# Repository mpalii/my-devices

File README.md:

Welcome to the repository with my embedded projects! 🚀

This repository serves as a collection of various embedded systems projects. Whether you're a hobbyist, student, or professional embedded developer, you'll find a diverse range of projects here, spanning across different microcontrollers, development boards, and applications.

Each project within this repository is meticulously crafted to showcase innovative ideas, practical implementations, and efficient utilization of embedded hardware and software. From IoT devices to robotics, sensor applications to automation systems, this repository covers a broad spectrum of embedded technologies.

Feel free to explore, learn, and contribute to the projects. Whether you're looking for inspiration, want to share your own projects, or collaborate with fellow enthusiasts, you've come to the right place. Don't hesitate to fork, clone, or submit pull requests!

Let's build amazing embedded systems together! 💡🛠️

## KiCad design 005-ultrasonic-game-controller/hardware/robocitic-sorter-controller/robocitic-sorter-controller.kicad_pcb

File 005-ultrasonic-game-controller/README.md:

# Gesture-Based Bluetooth Game Controller for Android

Experience touchless control and intuitive gameplay on your Android device!

This wireless game controller is powered by an **ATmega328P** microcontroller and uses an **HC-SR04 ultrasonic sensor** to detect hand gestures as input. Communication is handled via the **HC-05 Bluetooth module**, enabling seamless pairing with Android devices.

Whether you're building a casual game controller, an accessibility tool, or an experimental interface, this project provides a simple and responsive solution for hands-free interaction.

## Features

- 🎮 **Android-compatible** wireless control  
- ✋ **Gesture input** using ultrasonic distance sensing  
- 🔗 **Bluetooth communication** via HC-05 module  
- ⚡ Based on the popular and low-power **ATmega328P MCU**  
- 🧩 Easy to integrate and customize

---

**Coming soon**: Circuit schematics, firmware code, and app integration guide.

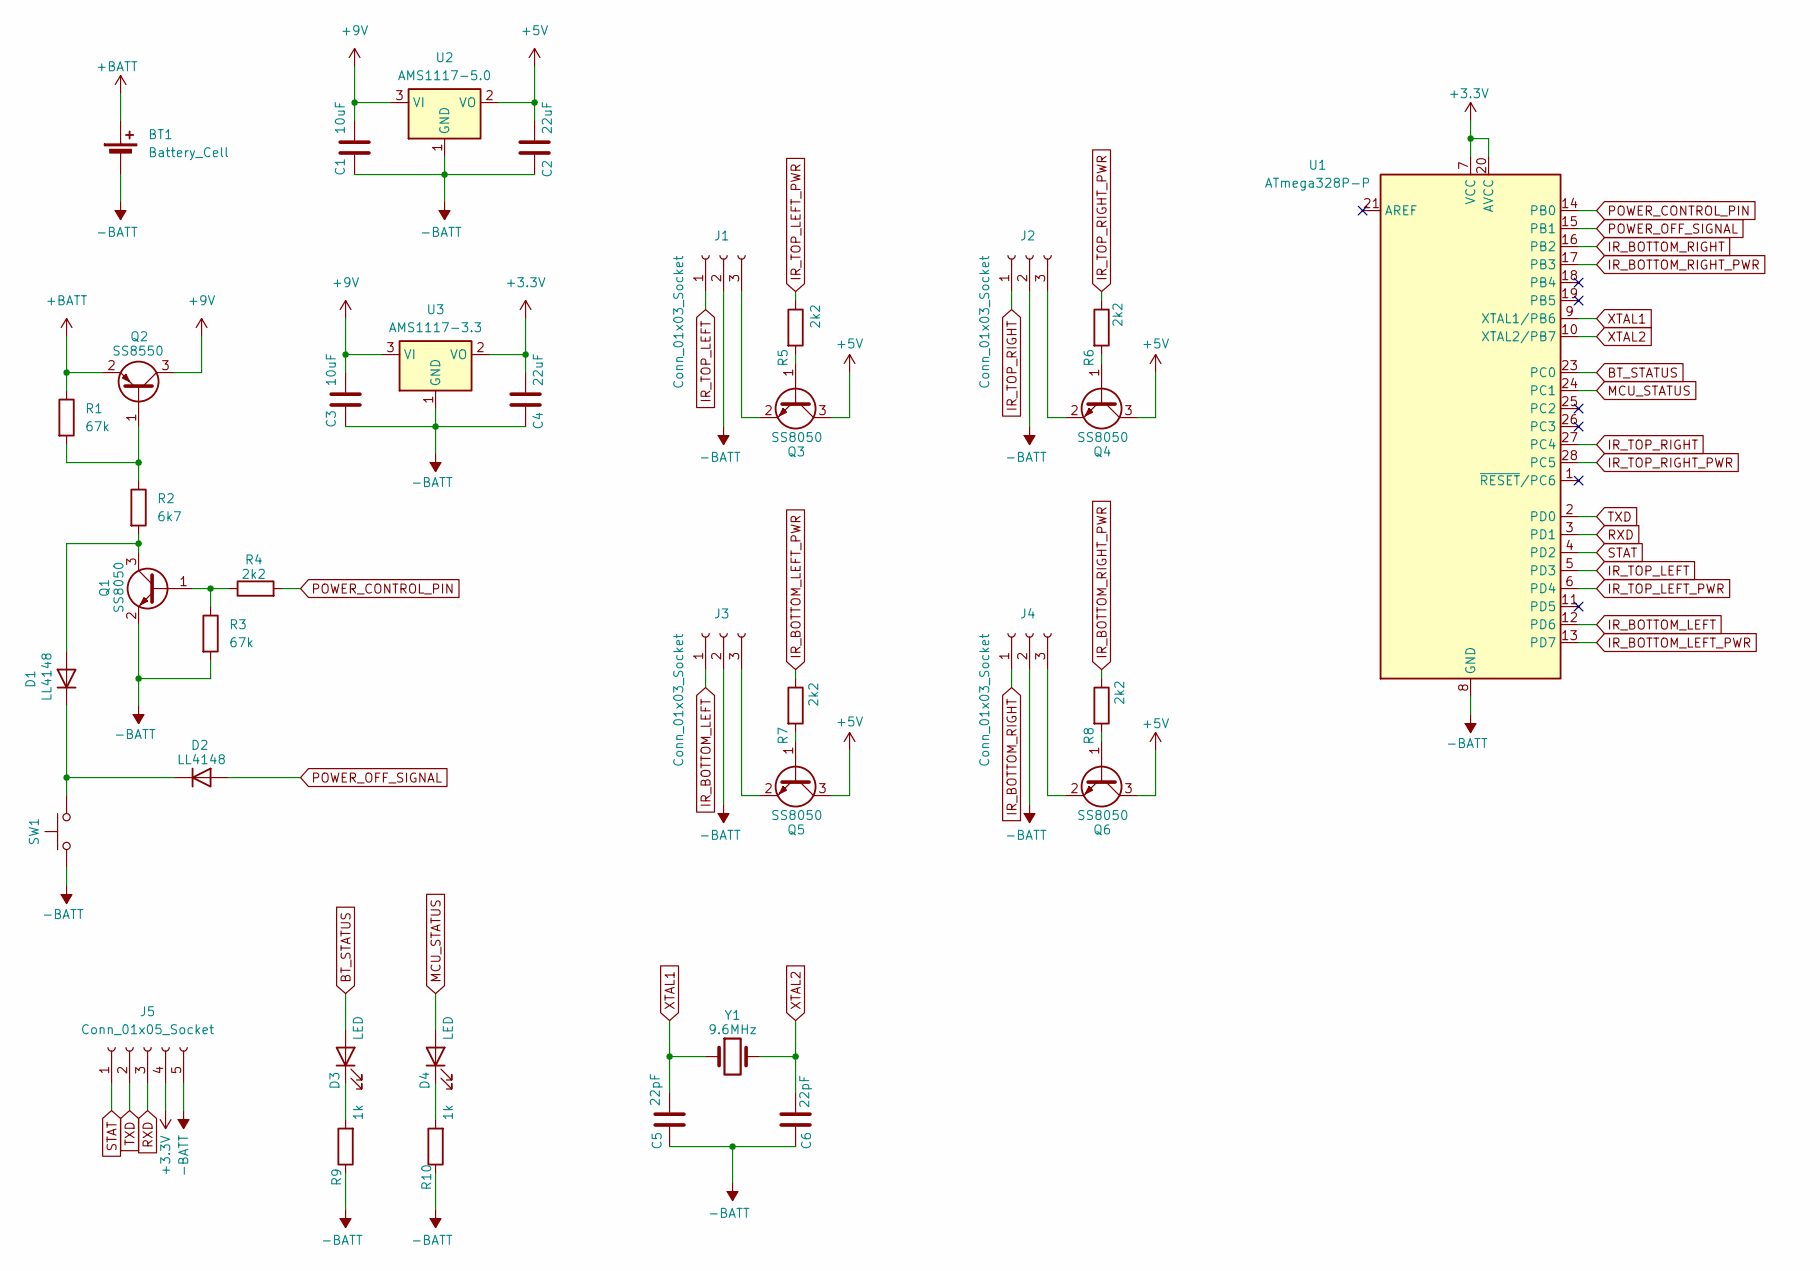
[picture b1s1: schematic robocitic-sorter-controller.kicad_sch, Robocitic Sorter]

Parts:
BT1: Battery_Cell; BatteryHolder_Eagle_12BH611-GR
C1, C3: 10uF; C_0805_2012Metric_Pad1.18x1.45mm_HandSolder
C2, C4: 22uF; C_0805_2012Metric_Pad1.18x1.45mm_HandSolder
C5, C6: 22pF; C_0805_2012Metric_Pad1.18x1.45mm_HandSolder
D1, D2: LL4148; D_MiniMELF_Handsoldering
D3, D4: LED; LED_0805_2012Metric_Pad1.15x1.40mm_HandSolder
J1, J2, J3, J4: Conn_01x03_Socket; PinSocket_1x03_P2.54mm_Vertical
J5: Conn_01x05_Socket; PinSocket_1x05_P2.54mm_Vertical
Q1, Q3, Q4, Q5, Q6: SS8050; SOT-23_Handsoldering
Q2: SS8550; SOT-23_Handsoldering
R1, R3: 67k; R_0805_2012Metric_Pad1.20x1.40mm_HandSolder
R2: 6k7; R_0805_2012Metric_Pad1.20x1.40mm_HandSolder
R4, R5, R6, R7, R8: 2k2; R_0805_2012Metric_Pad1.20x1.40mm_HandSolder
R9, R10: 1k; R_0805_2012Metric_Pad1.20x1.40mm_HandSolder
SW1: SW_Push; SW_PUSH_6mm_H5mm
U1: ATmega328P-P; DIP-28_W7.62mm_Socket_LongPads
U2: AMS1117-5.0; SOT-223-3_TabPin2
U3: AMS1117-3.3; SOT-223-3_TabPin2
Y1: 9.6MHz; Crystal_HC49-4H_Vertical

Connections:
+3.3V: C4.1, J5.4, U1.7 (VCC), U1.20 (AVCC), U3.2 (VO)
+5V: C2.1, Q3.3 (C), Q4.3 (C), Q5.3 (C), Q6.3 (C), U2.2 (VO)
+9V: C1.1, C3.1, Q2.3 (C), U2.3 (VI), U3.3 (VI)
+BATT: BT1.1 (+), Q2.2 (E), R1.1
-BATT: BT1.2 (-), C1.2, C2.2, C3.2, C4.2, C5.2, C6.2, J1.2, J2.2, J3.2, J4.2, J5.5, Q1.2 (E), R3.2, R9.1, R10.1, SW1.1, U1.8 (GND), U1.22 (GND), U2.1 (GND), U3.1 (GND)
BT_STATUS: D3.2 (A), U1.23 (PC0)
IR_BOTTOM_LEFT: J3.1, U1.12 (PD6)
IR_BOTTOM_LEFT_PWR: R7.1, U1.13 (PD7)
IR_BOTTOM_RIGHT: J4.1, U1.16 (PB2)
IR_BOTTOM_RIGHT_PWR: R8.1, U1.17 (PB3)
IR_TOP_LEFT: J1.1, U1.5 (PD3)
IR_TOP_LEFT_PWR: R5.1, U1.6 (PD4)
IR_TOP_RIGHT: J2.1, U1.27 (PC4)
IR_TOP_RIGHT_PWR: R6.1, U1.28 (PC5)
MCU_STATUS: D4.2 (A), U1.24 (PC1)
unnamed: D1.2 (A), Q1.3 (C), R2.2
unnamed: D1.1 (K), D2.1 (K), SW1.2
unnamed: D3.1 (K), R9.2
unnamed: D4.1 (K), R10.2
unnamed: J1.3, Q3.2 (E)
unnamed: J2.3, Q4.2 (E)
unnamed: J3.3, Q5.2 (E)
unnamed: J4.3, Q6.2 (E)
unnamed: Q1.1 (B), R3.1, R4.1
unnamed: Q2.1 (B), R1.2, R2.1
unnamed: Q3.1 (B), R5.2
unnamed: Q4.1 (B), R6.2
unnamed: Q5.1 (B), R7.2
unnamed: Q6.1 (B), R8.2
POWER_CONTROL_PIN: R4.2, U1.14 (PB0)
POWER_OFF_SIGNAL: D2.2 (A), U1.15 (PB1)
RXD: J5.3, U1.3 (PD1)
STAT: J5.1, U1.4 (PD2)
TXD: J5.2, U1.2 (PD0)
XTAL1: C5.1, U1.9 (XTAL1/PB6), Y1.1
XTAL2: C6.1, U1.10 (XTAL2/PB7), Y1.2

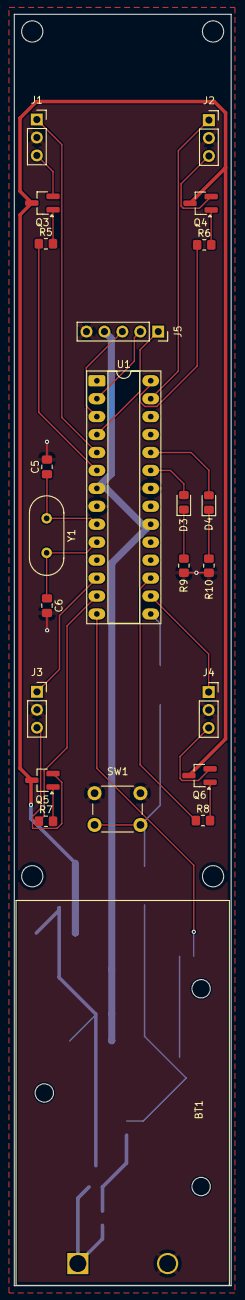
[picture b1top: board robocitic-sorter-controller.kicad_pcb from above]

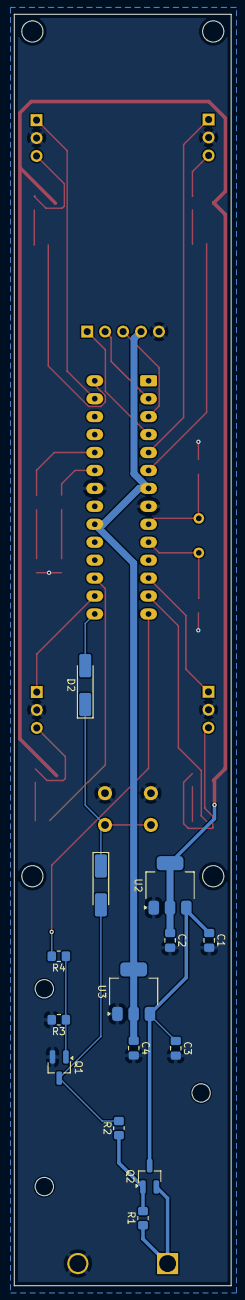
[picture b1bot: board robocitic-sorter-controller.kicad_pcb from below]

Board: 2 copper layers, 30.7 x 180.0 mm, 37 parts (14 on the bottom side), 36 nets.

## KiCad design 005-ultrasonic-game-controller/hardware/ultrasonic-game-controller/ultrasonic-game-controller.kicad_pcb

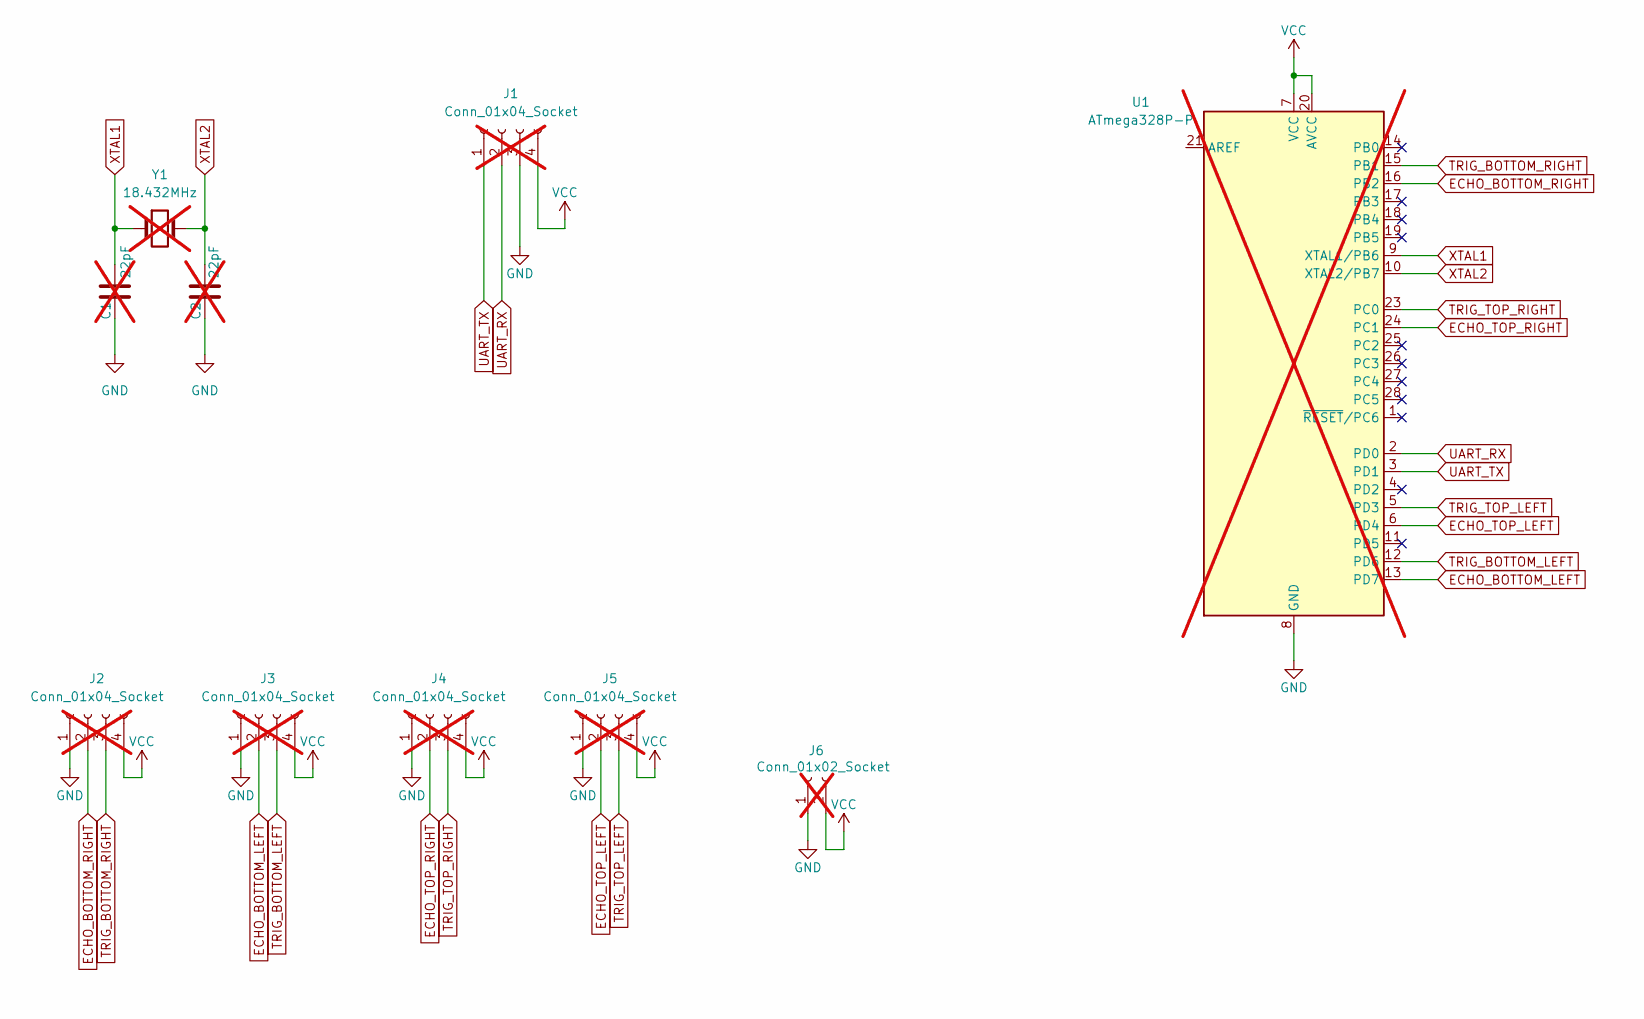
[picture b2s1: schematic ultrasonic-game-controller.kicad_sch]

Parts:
C1, C2: 22pF; C_0805_2012Metric_Pad1.18x1.45mm_HandSolder; not fitted
J1: Conn_01x04_Socket; PinSocket_1x04_P2.54mm_Horizontal; not fitted
J2, J3, J4, J5: Conn_01x04_Socket; PinSocket_1x04_P2.54mm_Vertical; not fitted
J6: Conn_01x02_Socket; PinSocket_1x02_P2.54mm_Vertical; not fitted
U1: ATmega328P-P; DIP-28_W7.62mm_Socket_LongPads; not fitted
Y1: 18.432MHz; Crystal_HC49-4H_Vertical; not fitted

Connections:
ECHO_BOTTOM_LEFT: J3.2, U1.13 (PD7)
ECHO_BOTTOM_RIGHT: J2.2, U1.16 (PB2)
ECHO_TOP_LEFT: J5.2, U1.6 (PD4)
ECHO_TOP_RIGHT: J4.2, U1.24 (PC1)
GND: C1.2, C2.2, J1.3, J2.1, J3.1, J4.1, J5.1, J6.1, U1.8 (GND), U1.22 (GND)
TRIG_BOTTOM_LEFT: J3.3, U1.12 (PD6)
TRIG_BOTTOM_RIGHT: J2.3, U1.15 (PB1)
TRIG_TOP_LEFT: J5.3, U1.5 (PD3)
TRIG_TOP_RIGHT: J4.3, U1.23 (PC0)
UART_RX: J1.2, U1.2 (PD0)
UART_TX: J1.1, U1.3 (PD1)
VCC: J1.4, J2.4, J3.4, J4.4, J5.4, J6.2, U1.7 (VCC), U1.20 (AVCC)
XTAL1: C1.1, U1.9 (XTAL1/PB6), Y1.1
XTAL2: C2.1, U1.10 (XTAL2/PB7), Y1.2

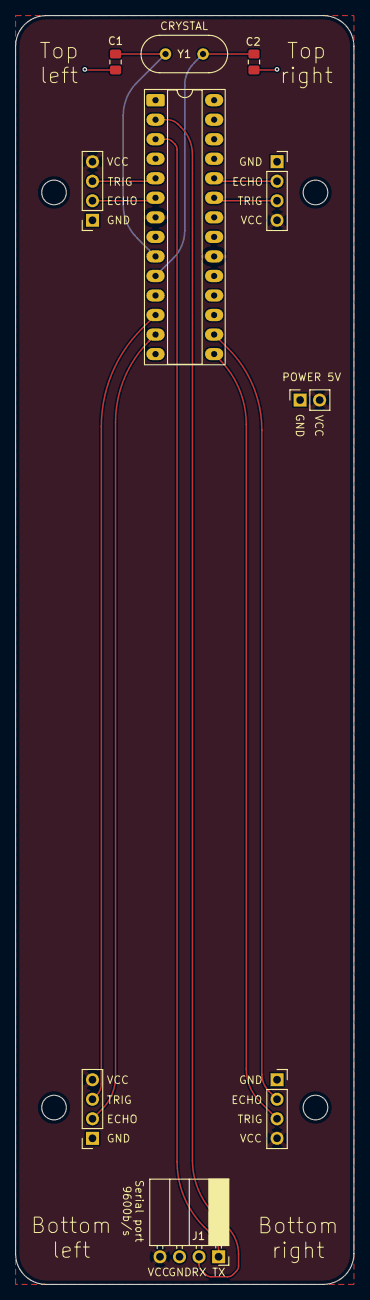
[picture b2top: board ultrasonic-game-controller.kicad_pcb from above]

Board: 2 copper layers, 44.0 x 165.0 mm, 10 parts (0 on the bottom side), 14 nets.

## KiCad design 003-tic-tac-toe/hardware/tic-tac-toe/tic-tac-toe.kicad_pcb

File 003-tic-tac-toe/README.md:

# 003-tic-tac-toe

As a starting point for this project I picked the implementation of [Jim Heaney - Tic Tac Toe](https://github.com/JimHeaney/tic-tac-toe-soldering-kit).  

Difference between Jim's and my versions:
- using SMD components (leds, resistors, capacitors);  
- two selectable playing modes: player versus palyer, player versus algorithm.

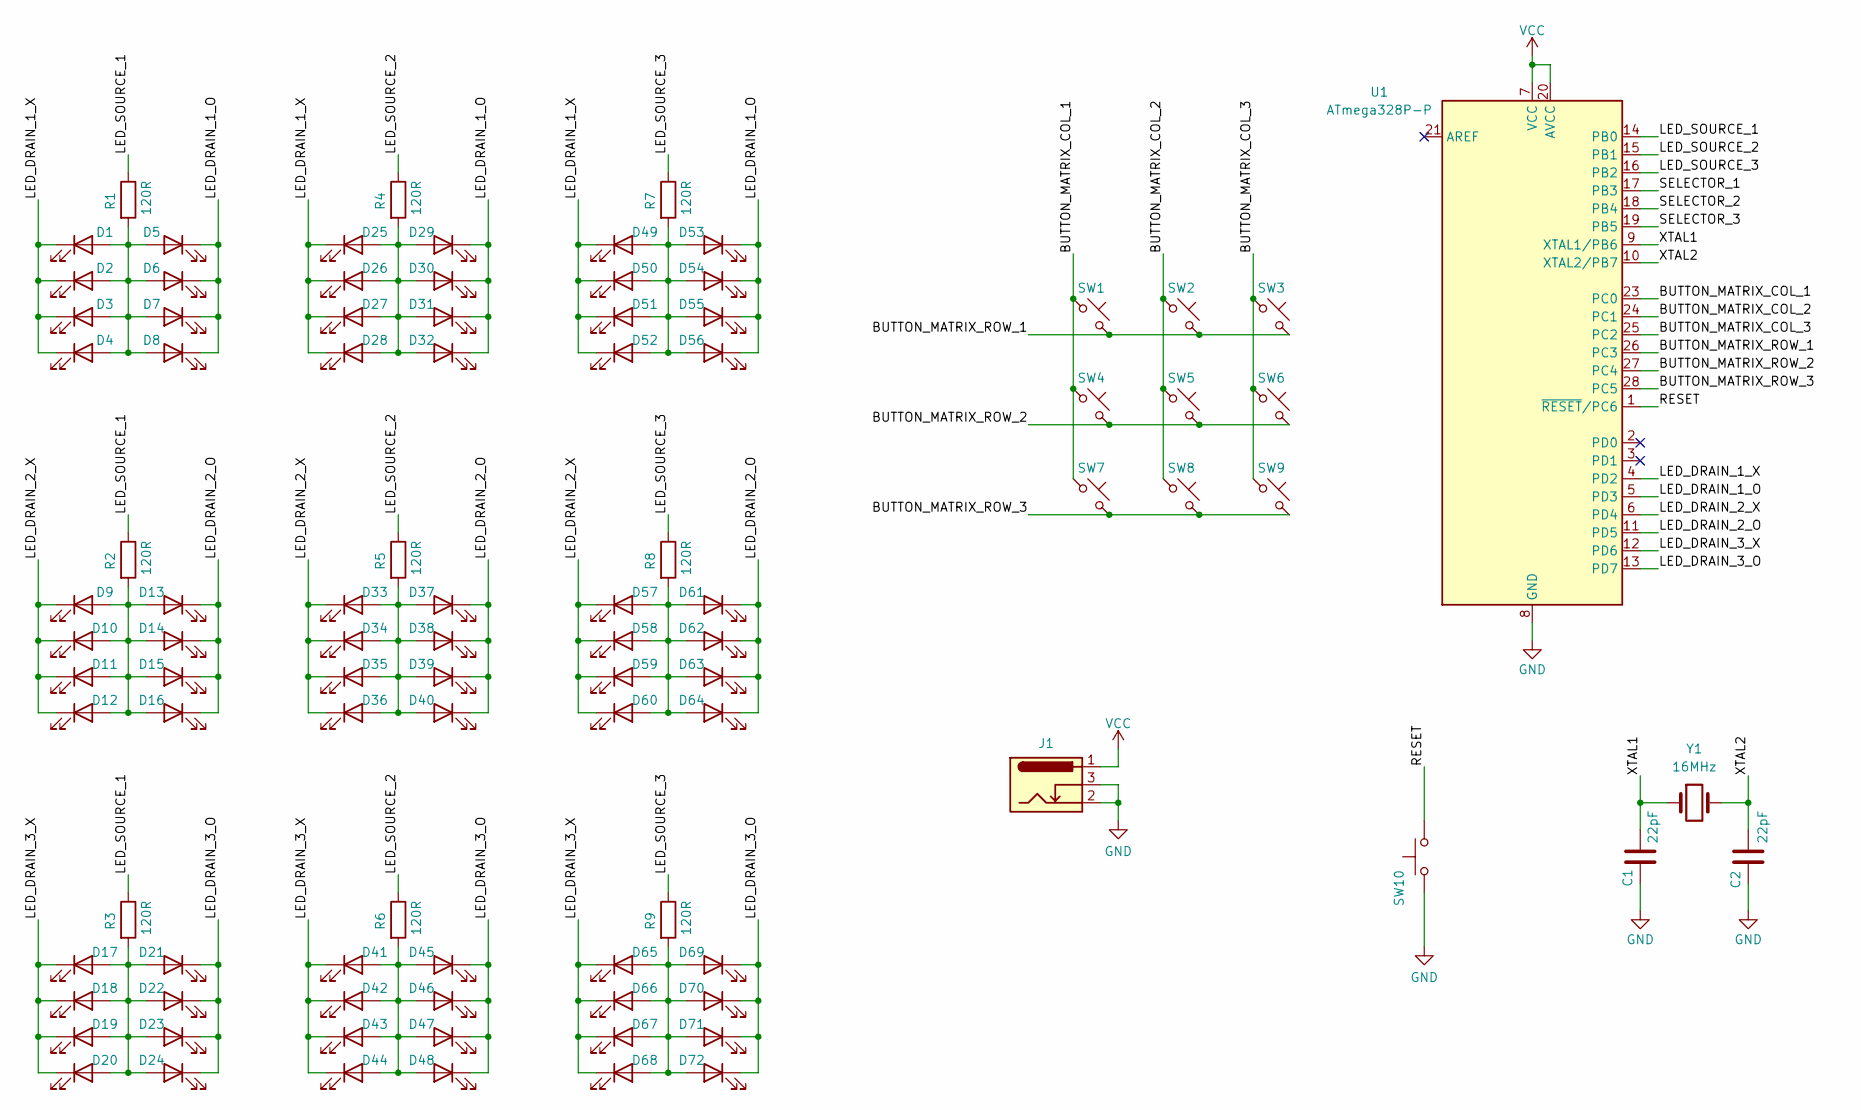
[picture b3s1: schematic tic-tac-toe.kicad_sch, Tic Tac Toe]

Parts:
C1, C2: 22pF; C_0805_2012Metric_Pad1.18x1.45mm_HandSolder
D1, D2, D3, D4, D5, D6, D7, D8, D9, D10, D11, D12, D13, D14, D15, D16, D17, D18, D19, D20, D21, D22, D23, D24, D25, D26, D27, D28, D29, D30, D31, D32, D33, D34, D35, D36, D37, D38, D39, D40, D41, D42, D43, D44, D45, D46, D47, D48, D49, D50, D51, D52, D53, D54, D55, D56, D57, D58, D59, D60, D61, D62, D63, D64, D65, D66, D67, D68, D69, D70, D71, D72: LED; LED_0805_2012Metric_Pad1.15x1.40mm_HandSolder
J1: Barrel_Jack_Switch; BarrelJack_GCT_DCJ200-10-A_Horizontal
R1, R2, R3, R4, R5, R6, R7, R8, R9: 120R; R_0805_2012Metric_Pad1.20x1.40mm_HandSolder
SW1, SW2, SW3, SW4, SW5, SW6, SW7, SW8, SW9: SW_Push_45deg; SW_PUSH_6mm_H5mm
SW10: SW_Push; SW_PUSH_6mm_H5mm
U1: ATmega328P-P; DIP-28_W7.62mm_Socket
Y1: 16MHz; Crystal_HC49-4H_Vertical

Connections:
/BUTTON_MATRIX_COL_1: SW1.1, SW4.1, SW7.1, U1.23 (PC0)
/BUTTON_MATRIX_COL_2: SW2.1, SW5.1, SW8.1, U1.24 (PC1)
/BUTTON_MATRIX_COL_3: SW3.1, SW6.1, SW9.1, U1.25 (PC2)
/BUTTON_MATRIX_ROW_1: SW1.2, SW2.2, SW3.2, U1.26 (PC3)
/BUTTON_MATRIX_ROW_2: SW4.2, SW5.2, SW6.2, U1.27 (PC4)
/BUTTON_MATRIX_ROW_3: SW7.2, SW8.2, SW9.2, U1.28 (PC5)
/LED_DRAIN_1_O: D5.1 (K), D6.1 (K), D7.1 (K), D8.1 (K), D29.1 (K), D30.1 (K), D31.1 (K), D32.1 (K), D53.1 (K), D54.1 (K), D55.1 (K), D56.1 (K), U1.5 (PD3)
/LED_DRAIN_1_X: D1.1 (K), D2.1 (K), D3.1 (K), D4.1 (K), D25.1 (K), D26.1 (K), D27.1 (K), D28.1 (K), D49.1 (K), D50.1 (K), D51.1 (K), D52.1 (K), U1.4 (PD2)
/LED_DRAIN_2_O: D13.1 (K), D14.1 (K), D15.1 (K), D16.1 (K), D37.1 (K), D38.1 (K), D39.1 (K), D40.1 (K), D61.1 (K), D62.1 (K), D63.1 (K), D64.1 (K), U1.11 (PD5)
/LED_DRAIN_2_X: D9.1 (K), D10.1 (K), D11.1 (K), D12.1 (K), D33.1 (K), D34.1 (K), D35.1 (K), D36.1 (K), D57.1 (K), D58.1 (K), D59.1 (K), D60.1 (K), U1.6 (PD4)
/LED_DRAIN_3_O: D21.1 (K), D22.1 (K), D23.1 (K), D24.1 (K), D45.1 (K), D46.1 (K), D47.1 (K), D48.1 (K), D69.1 (K), D70.1 (K), D71.1 (K), D72.1 (K), U1.13 (PD7)
/LED_DRAIN_3_X: D17.1 (K), D18.1 (K), D19.1 (K), D20.1 (K), D41.1 (K), D42.1 (K), D43.1 (K), D44.1 (K), D65.1 (K), D66.1 (K), D67.1 (K), D68.1 (K), U1.12 (PD6)
/LED_SOURCE_1: R1.1, R2.1, R3.1, U1.14 (PB0)
/LED_SOURCE_2: R4.1, R5.1, R6.1, U1.15 (PB1)
/LED_SOURCE_3: R7.1, R8.1, R9.1, U1.16 (PB2)
/RESET: SW10.2, U1.1 (~RESET/PC6)
/SELECTOR_1: U1.17 (PB3)
/SELECTOR_2: U1.18 (PB4)
/SELECTOR_3: U1.19 (PB5)
/XTAL1: C1.1, U1.9 (XTAL1/PB6), Y1.1
/XTAL2: C2.1, U1.10 (XTAL2/PB7), Y1.2
GND: C1.2, C2.2, J1.2, J1.3, SW10.1, U1.8 (GND), U1.22 (GND)
unnamed: D1.2 (A), D2.2 (A), D3.2 (A), D4.2 (A), D5.2 (A), D6.2 (A), D7.2 (A), D8.2 (A), R1.2
unnamed: D9.2 (A), D10.2 (A), D11.2 (A), D12.2 (A), D13.2 (A), D14.2 (A), D15.2 (A), D16.2 (A), R2.2
unnamed: D17.2 (A), D18.2 (A), D19.2 (A), D20.2 (A), D21.2 (A), D22.2 (A), D23.2 (A), D24.2 (A), R3.2
unnamed: D25.2 (A), D26.2 (A), D27.2 (A), D28.2 (A), D29.2 (A), D30.2 (A), D31.2 (A), D32.2 (A), R4.2
unnamed: D33.2 (A), D34.2 (A), D35.2 (A), D36.2 (A), D37.2 (A), D38.2 (A), D39.2 (A), D40.2 (A), R5.2
unnamed: D41.2 (A), D42.2 (A), D43.2 (A), D44.2 (A), D45.2 (A), D46.2 (A), D47.2 (A), D48.2 (A), R6.2
unnamed: D49.2 (A), D50.2 (A), D51.2 (A), D52.2 (A), D53.2 (A), D54.2 (A), D55.2 (A), D56.2 (A), R7.2
unnamed: D57.2 (A), D58.2 (A), D59.2 (A), D60.2 (A), D61.2 (A), D62.2 (A), D63.2 (A), D64.2 (A), R8.2
unnamed: D65.2 (A), D66.2 (A), D67.2 (A), D68.2 (A), D69.2 (A), D70.2 (A), D71.2 (A), D72.2 (A), R9.2
VCC: J1.1, U1.7 (VCC), U1.20 (AVCC)

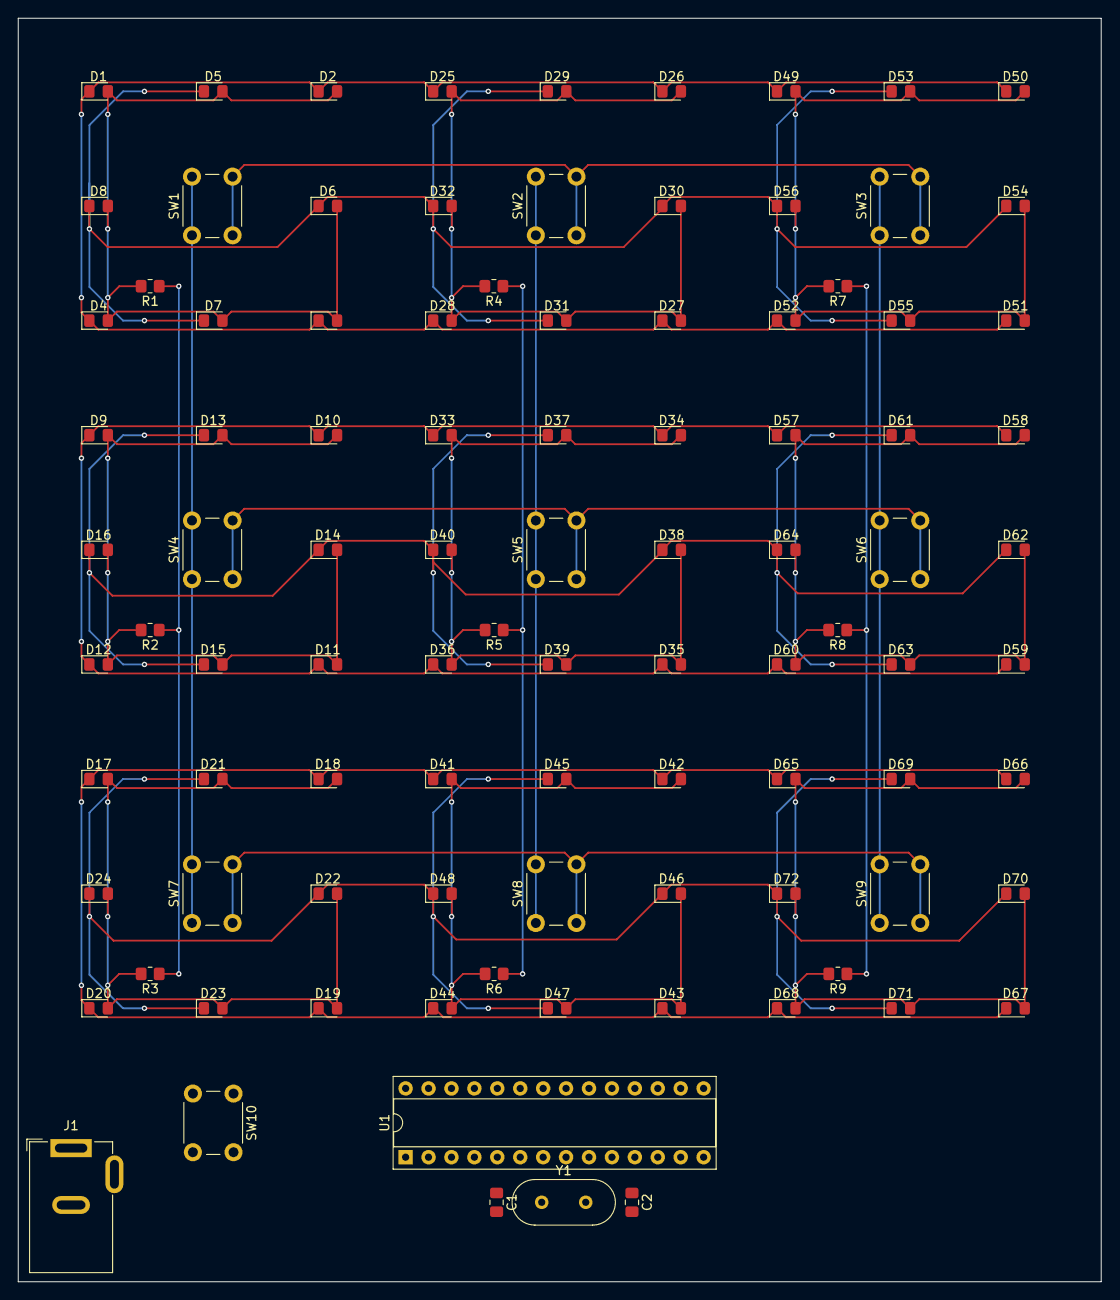
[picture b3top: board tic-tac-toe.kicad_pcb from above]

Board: 2 copper layers, 120.0 x 140.0 mm, 96 parts (0 on the bottom side), 29 nets.

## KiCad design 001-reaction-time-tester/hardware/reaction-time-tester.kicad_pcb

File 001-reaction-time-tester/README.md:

# Reaction Time Measurement System  

## Overview
This project implements a reaction time measurement system using an AVR microcontroller (mega328p). The system measures the time taken for a user to react to a stimulus and displays the results on an LCD screen.  
In fact this is an assigment for laboratory work #1 from Cornell University ECE 4760 course - Spring 2012.  

## Features
- **High Precision:** Measures reaction time with 16µs resolution.
- **User-Friendly Display:** Outputs results on an LCD screen.
- **Score Persistence:** Saves high scores in EEPROM memory.
- **PC Connectivity:** UART communication for monitoring and debugging.

## How to Use
1. **Hardware Setup:**
   - Connect the AVR microcontroller to the required peripherals (buttons, LCD, buzzer, etc.).
   - Assemble the PCB as outlined in the KiCad design files.

2. **Firmware Deployment:**
   - Use the provided `Makefile` to build the project using the AVR GCC toolchain.
   - Upload the firmware to the microcontroller using AVRDUDE.

3. **Operation:**
   - Power the device and follow the on-screen prompts.
   - Monitor reaction times on the LCD and see the system information using the UART interface.

4. **Simulation:**
   - Run the simulation using Proteus for testing and debugging without hardware.

## Dependencies
- AVR GCC Toolchain
- AVRDUDE for uploading firmware
- Terminal program for UART communication

## License
This project is licensed under the [MIT License](LICENSE).

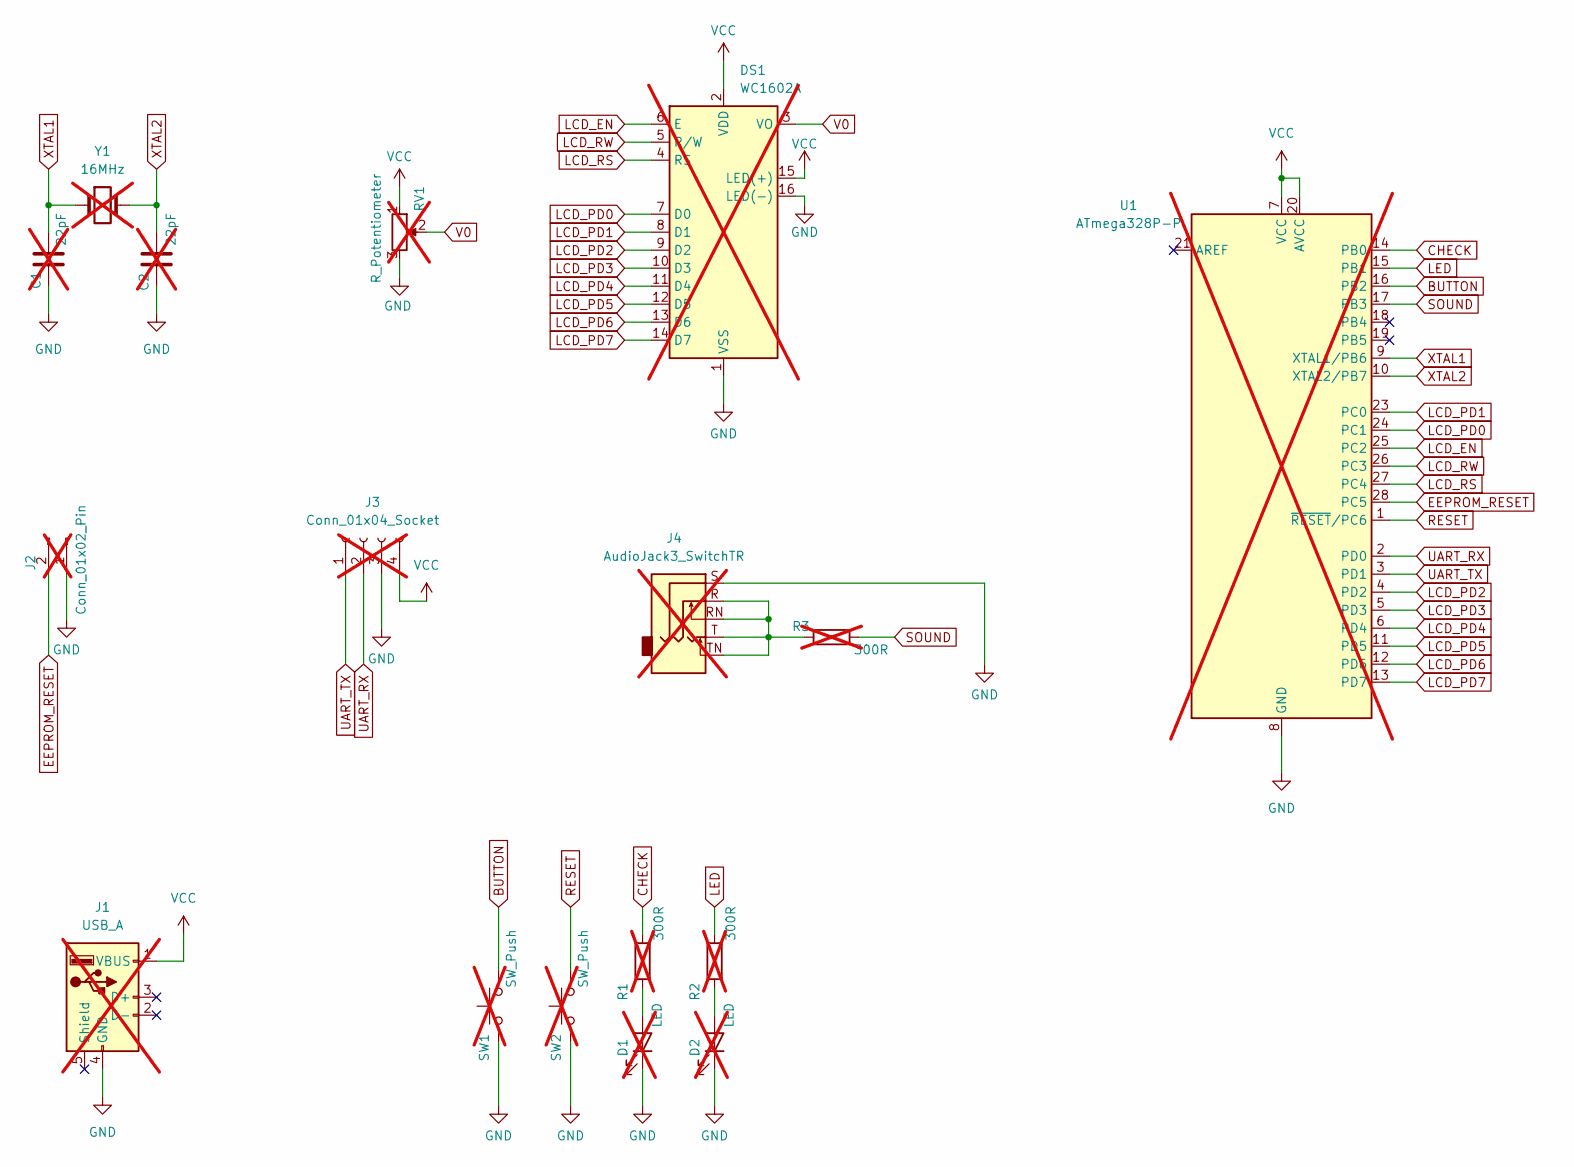
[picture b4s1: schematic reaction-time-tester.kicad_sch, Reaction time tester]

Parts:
C1, C2: 22pF; C_0805_2012Metric_Pad1.18x1.45mm_HandSolder; not fitted
D1, D2: LED; LED_0805_2012Metric_Pad1.15x1.40mm_HandSolder; not fitted
DS1: WC1602A; not fitted
J1: USB_A; USB_A_CONNFLY_DS1095-WNR0; not fitted
J2: Conn_01x02_Pin; PinHeader_1x02_P2.54mm_Vertical; not fitted
J3: Conn_01x04_Socket; PinSocket_1x04_P2.54mm_Horizontal; not fitted
J4: AudioJack3_SwitchTR; Jack_3.5mm_CUI_SJ1-3525N_Horizontal; not fitted
R1, R2, R3: 300R; R_0805_2012Metric_Pad1.20x1.40mm_HandSolder; not fitted
RV1: R_Potentiometer; Potentiometer_Bourns_3296W_Vertical; not fitted
SW1, SW2: SW_Push; SW_PUSH_6mm_H5mm; not fitted
U1: ATmega328P-P; DIP-28_W7.62mm_Socket; not fitted
Y1: 16MHz; Crystal_HC49-4H_Vertical; not fitted

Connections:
BUTTON: SW1.2, U1.16 (PB2)
CHECK: R1.2, U1.14 (PB0)
EEPROM_RESET: J2.2, U1.28 (PC5)
GND: C1.2, C2.2, D1.1 (K), D2.1 (K), DS1.1 (VSS), DS1.16 (LED(-)), J1.4 (GND), J2.1, J3.3, J4.S, RV1.3, SW1.1, SW2.1, U1.8 (GND), U1.22 (GND)
LCD_EN: DS1.6 (E), U1.25 (PC2)
LCD_PD0: DS1.7 (D0), U1.24 (PC1)
LCD_PD1: DS1.8 (D1), U1.23 (PC0)
LCD_PD2: DS1.9 (D2), U1.4 (PD2)
LCD_PD3: DS1.10 (D3), U1.5 (PD3)
LCD_PD4: DS1.11 (D4), U1.6 (PD4)
LCD_PD5: DS1.12 (D5), U1.11 (PD5)
LCD_PD6: DS1.13 (D6), U1.12 (PD6)
LCD_PD7: DS1.14 (D7), U1.13 (PD7)
LCD_RS: DS1.4 (RS), U1.27 (PC4)
LCD_RW: DS1.5 (R/W), U1.26 (PC3)
LED: R2.2, U1.15 (PB1)
unnamed: D1.2 (A), R1.1
unnamed: D2.2 (A), R2.1
unnamed: J4.R, J4.RN, J4.T, J4.TN, R3.2
RESET: SW2.2, U1.1 (~RESET/PC6)
SOUND: R3.1, U1.17 (PB3)
UART_RX: J3.2, U1.2 (PD0)
UART_TX: J3.1, U1.3 (PD1)
V0: DS1.3 (VO), RV1.2
VCC: DS1.2 (VDD), DS1.15 (LED(+)), J1.1 (VBUS), J3.4, RV1.1, U1.7 (VCC), U1.20 (AVCC)
XTAL1: C1.1, U1.9 (XTAL1/PB6), Y1.1
XTAL2: C2.1, U1.10 (XTAL2/PB7), Y1.2

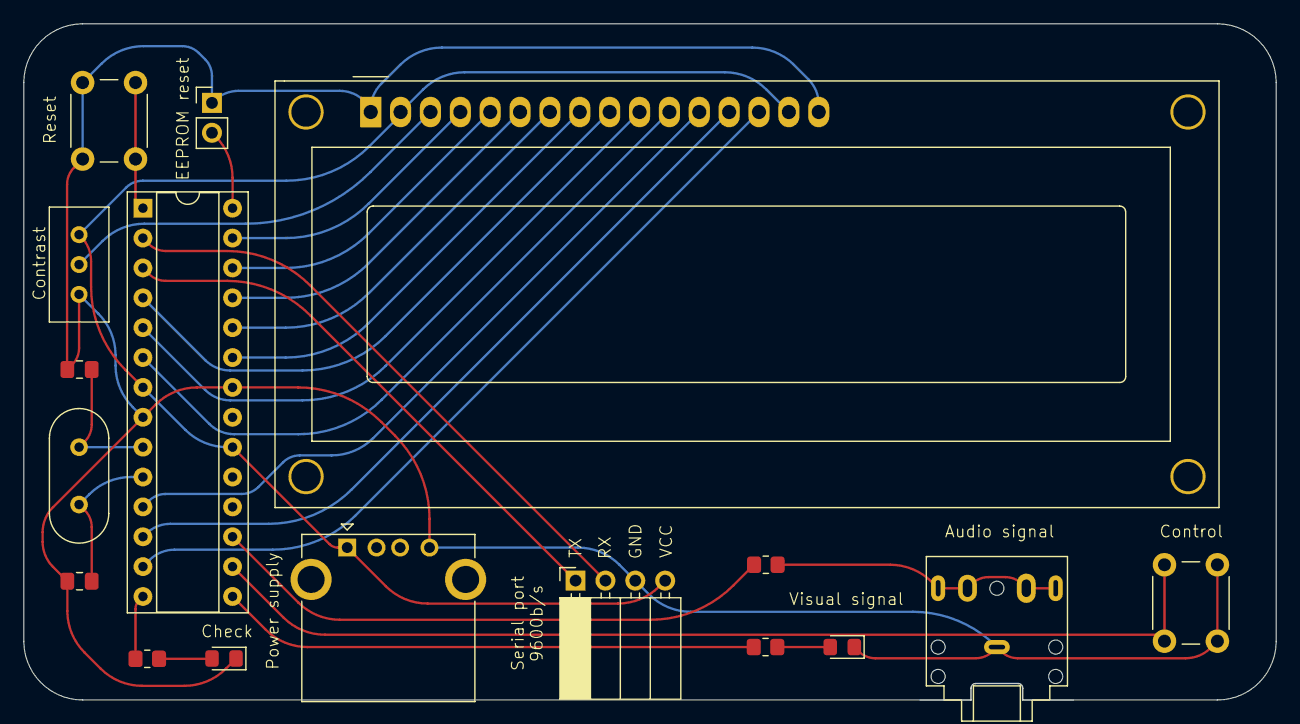
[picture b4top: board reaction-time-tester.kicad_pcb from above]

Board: 2 copper layers, 106.5 x 57.5 mm, 17 parts (0 on the bottom side), 27 nets.

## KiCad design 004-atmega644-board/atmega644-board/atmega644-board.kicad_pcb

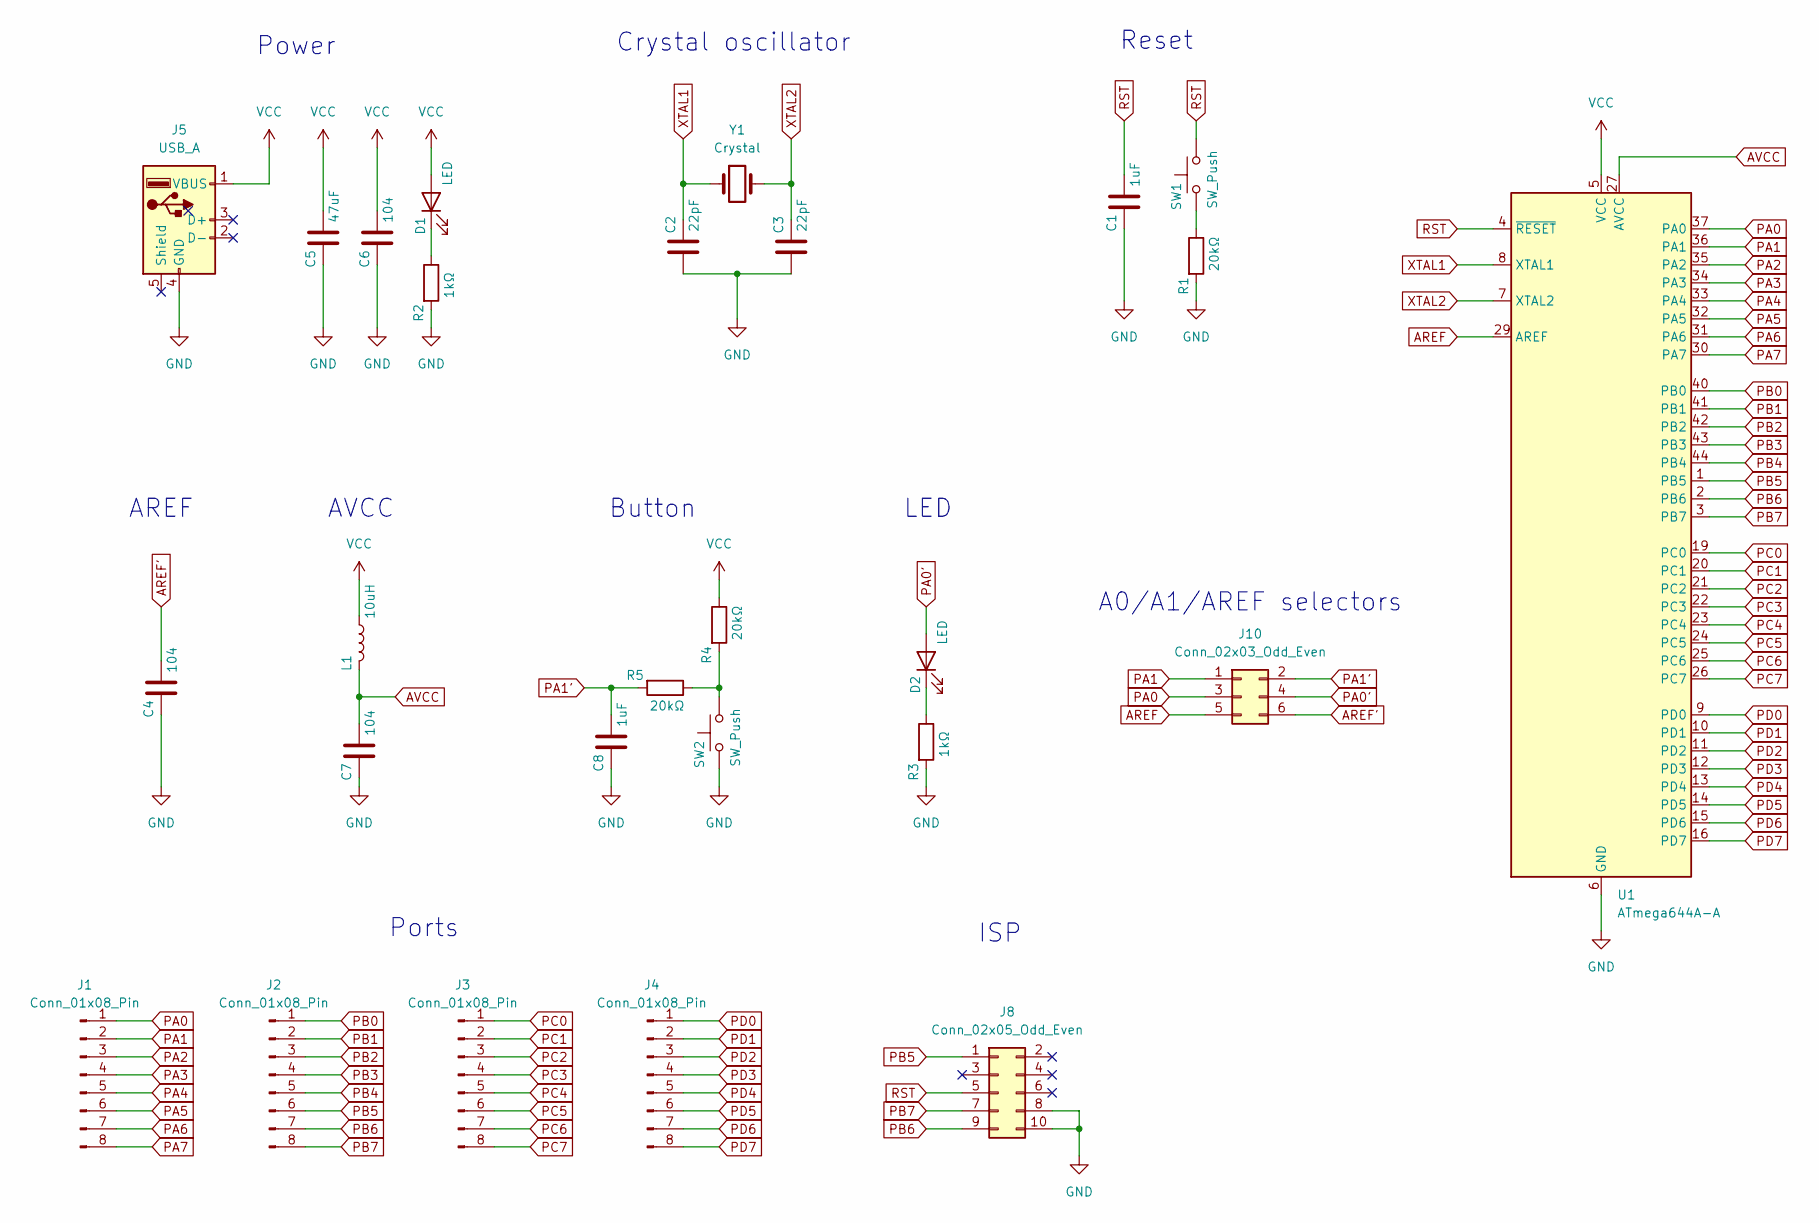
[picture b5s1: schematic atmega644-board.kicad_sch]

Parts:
C1, C8: 1uF; C_0805_2012Metric_Pad1.18x1.45mm_HandSolder
C2, C3: 22pF; C_0805_2012Metric_Pad1.18x1.45mm_HandSolder
C4, C6, C7: 104; C_0805_2012Metric_Pad1.18x1.45mm_HandSolder
C5: 47uF; C_0805_2012Metric_Pad1.18x1.45mm_HandSolder
D1, D2: LED; LED_0805_2012Metric_Pad1.15x1.40mm_HandSolder
J1, J2, J3, J4: Conn_01x08_Pin; PinHeader_1x08_P2.54mm_Vertical
J5: USB_A; USB_A_CONNFLY_DS1095-WNR0
J8: Conn_02x05_Odd_Even; PinHeader_2x05_P2.54mm_Vertical
J10: Conn_02x03_Odd_Even; PinHeader_2x03_P2.54mm_Vertical
L1: 10uH; L_0805_2012Metric_Pad1.15x1.40mm_HandSolder
R1, R4, R5: 20kΩ; R_0805_2012Metric_Pad1.20x1.40mm_HandSolder
R2, R3: 1kΩ; R_0805_2012Metric_Pad1.20x1.40mm_HandSolder
SW1: SW_Push; SW_PUSH_6mm_H4.3mm
SW2: SW_Push; SW_PUSH_6mm
U1: ATmega644A-A; TQFP-44_10x10mm_P0.8mm
Y1: Crystal; Crystal_HC49-4H_Vertical

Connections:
AREF: J10.5, U1.29 (AREF)
AREF': C4.1, J10.6
AVCC: C7.1, L1.2, U1.27 (AVCC)
GND: C1.2, C2.2, C3.2, C4.2, C5.2, C6.2, C7.2, C8.2, J5.4 (GND), J8.8, J8.10, R1.2, R2.2, R3.2, SW2.1, U1.6 (GND), U1.18 (GND), U1.28 (GND), U1.39 (GND)
unnamed: D1.1 (K), R2.1
unnamed: D2.1 (K), R3.1
unnamed: R1.1, SW1.1
unnamed: R4.2, R5.1, SW2.2
PA0: J1.1, J10.3, U1.37 (PA0)
PA0': D2.2 (A), J10.4
PA1: J1.2, J10.1, U1.36 (PA1)
PA1': C8.1, J10.2, R5.2
PA2: J1.3, U1.35 (PA2)
PA3: J1.4, U1.34 (PA3)
PA4: J1.5, U1.33 (PA4)
PA5: J1.6, U1.32 (PA5)
PA6: J1.7, U1.31 (PA6)
PA7: J1.8, U1.30 (PA7)
PB0: J2.1, U1.40 (PB0)
PB1: J2.2, U1.41 (PB1)
PB2: J2.3, U1.42 (PB2)
PB3: J2.4, U1.43 (PB3)
PB4: J2.5, U1.44 (PB4)
PB5: J2.6, J8.1, U1.1 (PB5)
PB6: J2.7, J8.9, U1.2 (PB6)
PB7: J2.8, J8.7, U1.3 (PB7)
PC0: J3.1, U1.19 (PC0)
PC1: J3.2, U1.20 (PC1)
PC2: J3.3, U1.21 (PC2)
PC3: J3.4, U1.22 (PC3)
PC4: J3.5, U1.23 (PC4)
PC5: J3.6, U1.24 (PC5)
PC6: J3.7, U1.25 (PC6)
PC7: J3.8, U1.26 (PC7)
PD0: J4.1, U1.9 (PD0)
PD1: J4.2, U1.10 (PD1)
PD2: J4.3, U1.11 (PD2)
PD3: J4.4, U1.12 (PD3)
PD4: J4.5, U1.13 (PD4)
PD5: J4.6, U1.14 (PD5)
PD6: J4.7, U1.15 (PD6)
PD7: J4.8, U1.16 (PD7)
RST: C1.1, J8.5, SW1.2, U1.4 (~RESET)
VCC: C5.1, C6.1, D1.2 (A), J5.1 (VBUS), L1.1, R4.1, U1.5 (VCC), U1.17 (VCC), U1.38 (VCC)
XTAL1: C2.1, U1.8 (XTAL1), Y1.1
XTAL2: C3.1, U1.7 (XTAL2), Y1.2

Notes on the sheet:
AREF
Crystal oscillator
ISP
Button
Power
LED
A0/A1/AREF selectors
AVCC
Reset
Ports

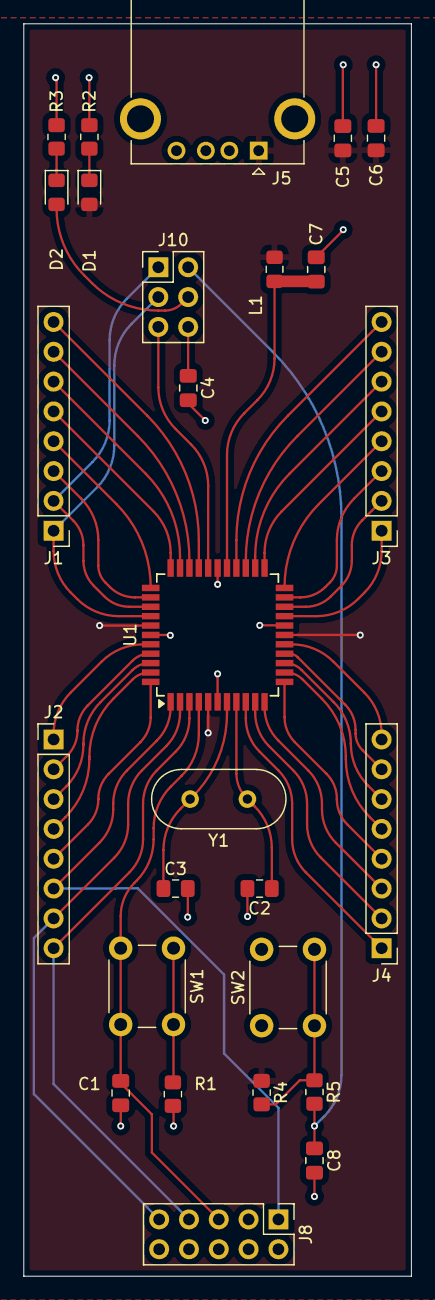
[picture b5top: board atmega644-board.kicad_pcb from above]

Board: 2 copper layers, 33.0 x 106.7 mm, 27 parts (0 on the bottom side), 46 nets.
